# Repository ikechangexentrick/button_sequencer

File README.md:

# button sequencer
4 channel gate sequencer

### [schematic](https://raw.githubusercontent.com/ikechangexentrick/button_sequencer/master/hw/button_sequencer_v1_schematic.pdf)

## Prerequisites

### Hardware
- ProMicro (Arduino micro clone)

### Software (Arduino libraries)
- [button](https://github.com/ikechangexentrick/button)
- [MsTimer2](https://github.com/PaulStoffregen/MsTimer2)

## Build instruction

... to be written ...

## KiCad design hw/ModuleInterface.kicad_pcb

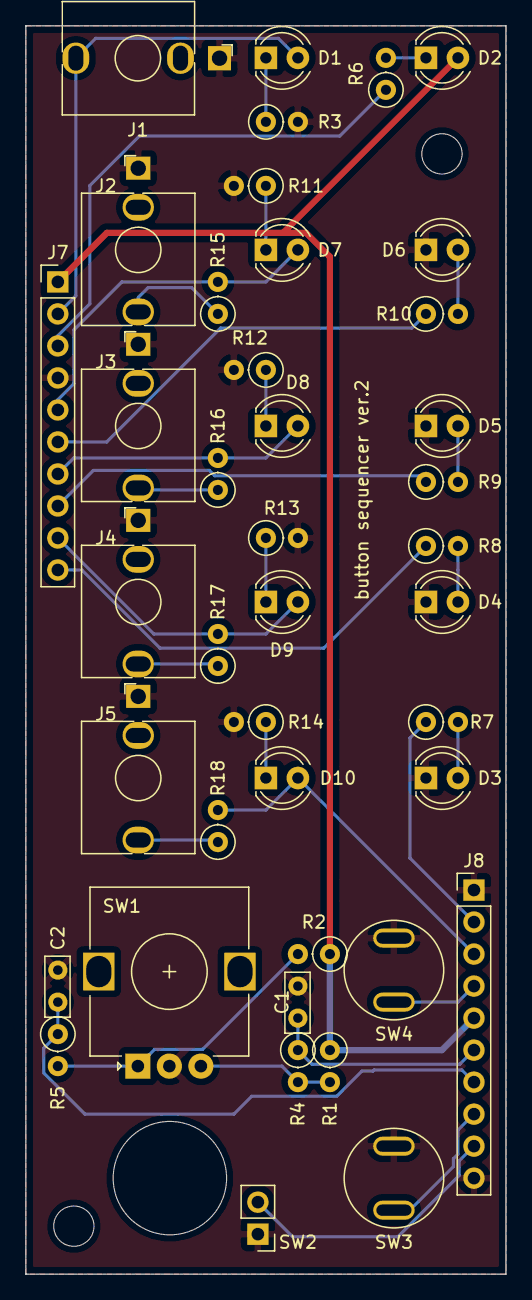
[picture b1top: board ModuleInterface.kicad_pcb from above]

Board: 2 copper layers, 38.1 x 99.1 mm, 41 parts (0 on the bottom side), 33 nets.

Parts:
C1, C2: 0.1u; C_Axial_L4.8mm_D2.0mm_P2.54mm_Horizontal
D1: clock; LED_D4.0mm
D2, D3: select4; LED_D4.0mm
D4: select3; LED_D4.0mm
D5: select2; LED_D4.0mm
D6: select1; LED_D4.0mm
D7: gate1; LED_D4.0mm
D8: gate2; LED_D4.0mm
D9: gate3; LED_D4.0mm
D10: gate4; LED_D4.0mm
J1: clock_in; mono_jack_3.5mm
J2: gate_out_1; mono_jack_3.5mm
J3: gate_out_2; mono_jack_3.5mm
J4: gate_out_3; mono_jack_3.5mm
J5: gate_out_4; mono_jack_3.5mm
J7: bus_L; PinHeader_1x10_P2.54mm_Vertical
J8: bus_R; PinHeader_1x10_P2.54mm_Vertical
R1, R2, R3, R4, R5: 10k; R_Axial_DIN0207_L6.3mm_D2.5mm_P2.54mm_Vertical
R6, R7, R8, R9, R10, R15, R16, R17, R18: 1k; R_Axial_DIN0207_L6.3mm_D2.5mm_P2.54mm_Vertical
R11, R12, R13, R14: 3.3k; R_Axial_DIN0207_L6.3mm_D2.5mm_P2.54mm_Vertical
SW1: Rotary_Encoder; RotaryEncoder_Alps_EC12E_Vertical_H20mm
SW2: enter; PinHeader_1x02_P2.54mm_Vertical
SW3: func2; push_button
SW4: function; push_button

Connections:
+5V: D2.2, J7.1, J8.5, R1.1, R2.1
/Sheet62419879/clock_in: D1.2, J1.T, J7.2
/Sheet62419879/gate_1: D7.2, J7.5, R15.2
/Sheet62419879/gate_2: D8.2, J7.7, R16.2
/Sheet62419879/gate_3: D9.2, J7.9, R17.2
/Sheet62419879/gate_4: D10.2, J8.3, R18.2
/Sheet62419879/re_1: C2.1, J8.7, R5.1
/Sheet62419879/re_2: C1.1, J8.6, R4.1
/Sheet62419879/select_1: J7.6, R10.1
/Sheet62419879/select_2: J7.8, R9.1
/Sheet62419879/select_3: J7.10, R8.1
/Sheet62419879/select_4: J8.2, R7.1
/Sheet62419879/seq_start: J7.3, R6.1
/Sheet62419879/sw_enter: J8.9, SW2.2
/Sheet62419879/sw_func_1: J8.4, SW4.2
/Sheet62419879/sw_func_2: J8.8, SW3.2
GND: C1.2, C2.2, D3.1, D4.1, D5.1, D6.1, J1.S, J2.S, J3.S, J4.S, J5.S, J7.4, J8.1, J8.10, R3.2, R11.2, R12.2, R13.2, R14.2, SW1.C, SW2.1, SW3.1, SW4.1
unnamed: D1.1, R3.1
unnamed: D2.1, R6.2
unnamed: D3.2, R7.2
unnamed: D4.2, R8.2
unnamed: D5.2, R9.2
unnamed: D6.2, R10.2
unnamed: D7.1, R11.1
unnamed: D8.1, R12.1
unnamed: D9.1, R13.1
unnamed: D10.1, R14.1
unnamed: J2.T, R15.1
unnamed: J3.T, R16.1
unnamed: J4.T, R17.1
unnamed: J5.T, R18.1
unnamed: R1.2, R4.2, SW1.B
unnamed: R2.2, R5.2, SW1.A

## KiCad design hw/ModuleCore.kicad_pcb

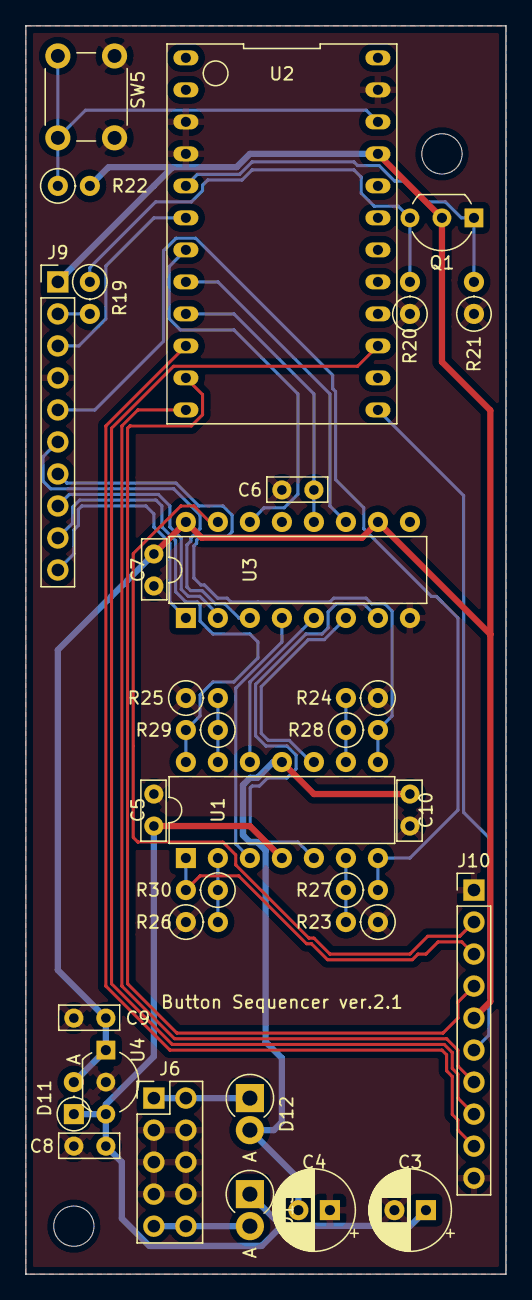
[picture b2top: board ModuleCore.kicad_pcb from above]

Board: 2 copper layers, 38.1 x 99.1 mm, 32 parts (0 on the bottom side), 35 nets.

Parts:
C3, C4: 100u; CP_Radial_D6.3mm_P2.50mm
C5, C6, C7, C8, C9, C10: 0.1u; C_Axial_L4.8mm_D2.0mm_P2.54mm_Horizontal
D11: 1N4148; D_DO-35_SOD27_P2.54mm_Vertical_AnodeUp
D12, D13: D_Schottky; D_DO-15_P2.54mm_Vertical_AnodeUp
J6: power_bus; PinHeader_2x05_P2.54mm_Vertical
J9: bus_L; PinHeader_1x10_P2.54mm_Vertical
J10: bus_R; PinHeader_1x10_P2.54mm_Vertical
Q1: 2SC1815; TO-92_Inline_Wide
R19, R20, R21: 100k; R_Axial_DIN0207_L6.3mm_D2.5mm_P2.54mm_Vertical
R22, R23, R24, R25, R26, R27, R28, R29, R30: 10k; R_Axial_DIN0207_L6.3mm_D2.5mm_P2.54mm_Vertical
SW5: SW_Push; SW_PUSH_6mm
U1: TL074; DIP-14_W7.62mm
U2: ProMicro; Pro_Micro_Top_side_Up
U3: 74HC595; DIP-16_W7.62mm
U4: L78L05_TO92; TO-92_Inline_Wide

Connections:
+5V: C7.1, C9.2, D11.2, J9.1, J10.5, Q1.2, R22.2, U2.21, U3.10, U3.16, U4.1
+12V: C3.1, C5.1, C8.2, D11.1, D13.1, U1.4, U4.3
-12V: C4.2, C10.2, D12.2, U1.11
/Sheet62451AD7/595_clock: U2.8, U3.11
/Sheet62451AD7/595_data: U2.7, U3.14
/Sheet62451AD7/595_latch: C6.2, U2.9, U3.12
/Sheet62451AD7/clock: Q1.1, R21.2, U2.5
/Sheet62451AD7/clock_in: J9.2, R19.2
/Sheet62451AD7/gate1: U1.5, U3.7
/Sheet62451AD7/gate2: U1.10, U3.6
/Sheet62451AD7/gate3: U1.12, U3.5
/Sheet62451AD7/gate4: U1.3, U3.4
/Sheet62451AD7/gate_1: J9.5, R27.2, U1.7
/Sheet62451AD7/gate_2: J9.7, R28.2, U1.8
/Sheet62451AD7/gate_3: J9.9, R29.2, U1.14
/Sheet62451AD7/gate_4: J10.3, R30.2, U1.1
/Sheet62451AD7/re_1: J10.7, U2.12
/Sheet62451AD7/re_2: J10.6, U2.13
/Sheet62451AD7/select_1: J9.6, U3.3
/Sheet62451AD7/select_2: J9.8, U3.2
/Sheet62451AD7/select_3: J9.10, U3.1
/Sheet62451AD7/select_4: J10.2, U3.15
/Sheet62451AD7/seq_start: J9.3, U2.6
/Sheet62451AD7/sw_enter: J10.9, U2.10
/Sheet62451AD7/sw_func_1: J10.4, U2.11
/Sheet62451AD7/sw_func_2: J10.8, U2.15
GND: C3.2, C4.1, C5.2, C6.1, C7.2, C8.1, C9.1, C10.1, J6.3, J6.4, J6.5, J6.6, J6.7, J6.8, J9.4, J10.1, J10.10, R20.1, R21.1, R23.1, R24.1, R25.1, R26.1, SW5.2, U2.3, U2.4, U2.23, U3.8, U3.13, U4.2
unnamed: D12.1, J6.1, J6.2
unnamed: D13.2, J6.9, J6.10
unnamed: Q1.3, R19.1, R20.2
unnamed: R22.1, SW5.1, U2.22
unnamed: R23.2, R27.1, U1.6
unnamed: R24.2, R28.1, U1.9
unnamed: R25.2, R29.1, U1.13
unnamed: R26.2, R30.1, U1.2

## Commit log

2022-06-20 A clone of Antimatter LaunchCodes.
2022-06-20 Software: Fixed a bug - modified to output beats when pressing Enter button.
    Hardware: appended kicad project files.
2022-06-20 Modified to accomodate to the actual circuit, instead of the breadboard prototype.
2022-06-20 Appended config mode; keep press "func", then click "fill/clear" to enter. In the config mode, "slot" LED blinks. The slots correspond to config items (see below). Config value is indicated on "cycle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
    Appended ratchetting/retriggering; keep press "func", then click "enter".
2022-10-01 Added schematic pdf.
2022-10-01 branch for images on README.md
2022-10-01 Added README.md
2023-12-13 minor mods
2023-12-13 Added "live input" mode. Fixed a bug; reversed button's on/off.
